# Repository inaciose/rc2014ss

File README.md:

# rc2014ss - RC2014 PCB single sided for CNC 3018
This repository was to be dedicated to sharing a series of board schematics and layouts compatible with the RC2014 bus and which were designed to be produced on a 3018 CNC.

However, I have had difficulty completing this project, but I have continued to make addon boards on perforated boards. Therefore, this repository became a generic place where I document the different boards.

Boards designed for CNC 3018

- Z80 CPU - rcz80cpu
- 32K RAM - rc32kram62256
- 64K RAM - rc64kram2x62256
- ACIA 6551 - rc6551z80
- ROM 2K - rcrom28c16
- ROM 8K - rcrom28c64
- ACIA 60b50 - rcserial60b50ttl
- Z80 tester - rcz80test

To make a minimal system with just boards made with the CNC 3018, the only thing left to do is a simple plate for the clock. In any case, I plan to make versions for the CNC 3018 of the main perforated plates in the long term.

# Board production process at CNC 3018

- Draw schematic in EAGLE
- Design the board within the size restrictions
- Export gerber files
- Import the copper_bottom.gbr file into flatcam and produce gcode files for track isolation
- Import the drill_1_16.xln file into flatcam and produce the gcode files to drill the holes
- Open the candle, and proceed with the alignment from scratch, load the isolation file, place the probe and make the height map, remove the probe, and start cnc it. When it stop, change the tool, load the hole drill file and move on.

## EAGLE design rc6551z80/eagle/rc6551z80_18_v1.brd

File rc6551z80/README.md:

# CNC 3018 - RC2014 - ACIA 6551 BOARD

This board is not covered in the stock SCM (Small computer monitor).

I have done a modified version of SCM that works with it. 
I also have modified a 2K z80 monitor to work with it.

TODO: need to collect the software...

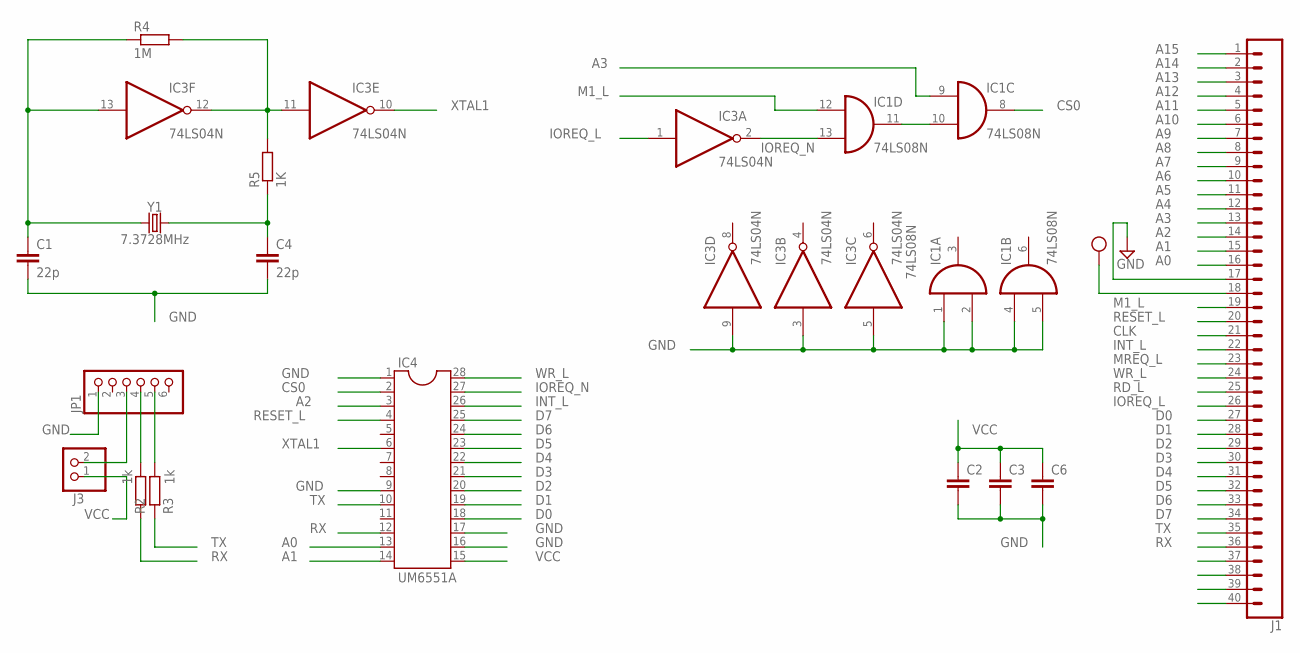
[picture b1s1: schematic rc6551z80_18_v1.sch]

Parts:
C1, C4: 22p; C025-024X044
C2, C3, C6: C-EU050-025X075; C050-025X075
IC1: 74LS08N; DIL14
IC3: 74LS04N; DIL14
IC4: UM6551A; DIL28-6
J1: CONN_40OFFSET; 1X40_OFFSET
J3: PINHD-1X2; 1X02
JP1: PINHD-1X6; 1X06
R2, R3: 1k; 0204/7
R4: 1M; 0204/7
R5: 1K; 0204/7
Y1: 7.3728MHz; HC49U

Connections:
A0: IC4.13, J1.16
A1: IC4.14, J1.15
A2: IC4.3, J1.14
A3: IC1.9 (I0), J1.13
A4: J1.12
A5: J1.11
A6: J1.10
A7: J1.9
A8: J1.8
A9: J1.7
A10: J1.6
A11: J1.5
A12: J1.4
A13: J1.3
A14: J1.2
A15: J1.1
CLK: J1.21
CS0: IC1.8 (O), IC4.2
D0: IC4.18, J1.27
D1: IC4.19, J1.28
D2: IC4.20, J1.29
D3: IC4.21, J1.30
D4: IC4.22, J1.31
D5: IC4.23, J1.32
D6: IC4.24, J1.33
D7: IC4.25, J1.34
GND: C1.2, C2.2, C3.2, C4.2, C6.2, IC1.1 (I0), IC1.2 (I1), IC1.4 (I0), IC1.5 (I1), IC1.7 (GND), IC3.3 (I), IC3.5 (I), IC3.7 (GND), IC3.9 (I), IC4.1, IC4.9, IC4.16, IC4.17, J1.17, JP1.1
INT_L: IC4.26, J1.22
IOREQ_L: IC3.1 (I), J1.26
IOREQ_N: IC1.13 (I1), IC3.2 (O), IC4.27
M1_L: IC1.12 (I0), J1.19
MREQ_L: J1.23
unnamed: J3.2, JP1.3
unnamed: JP1.4, R2.1
unnamed: JP1.5, R3.1
unnamed: C1.1, IC3.13 (I), R4.1, Y1.1
unnamed: C4.1, R5.1, Y1.2
unnamed: IC3.11 (I), IC3.12 (O), R4.2, R5.2
unnamed: IC1.10 (I1), IC1.11 (O)
RD_L: J1.25
RESET_L: IC4.4, J1.20
RX: IC4.12, J1.36, R2.2
TX: IC4.10, J1.35, R3.2
VCC: C2.1, C3.1, C6.1, IC1.14 (VCC), IC3.14 (VCC), IC4.15, J1.18, J3.1
WR_L: IC4.28, J1.24
XTAL1: IC3.10 (O), IC4.6

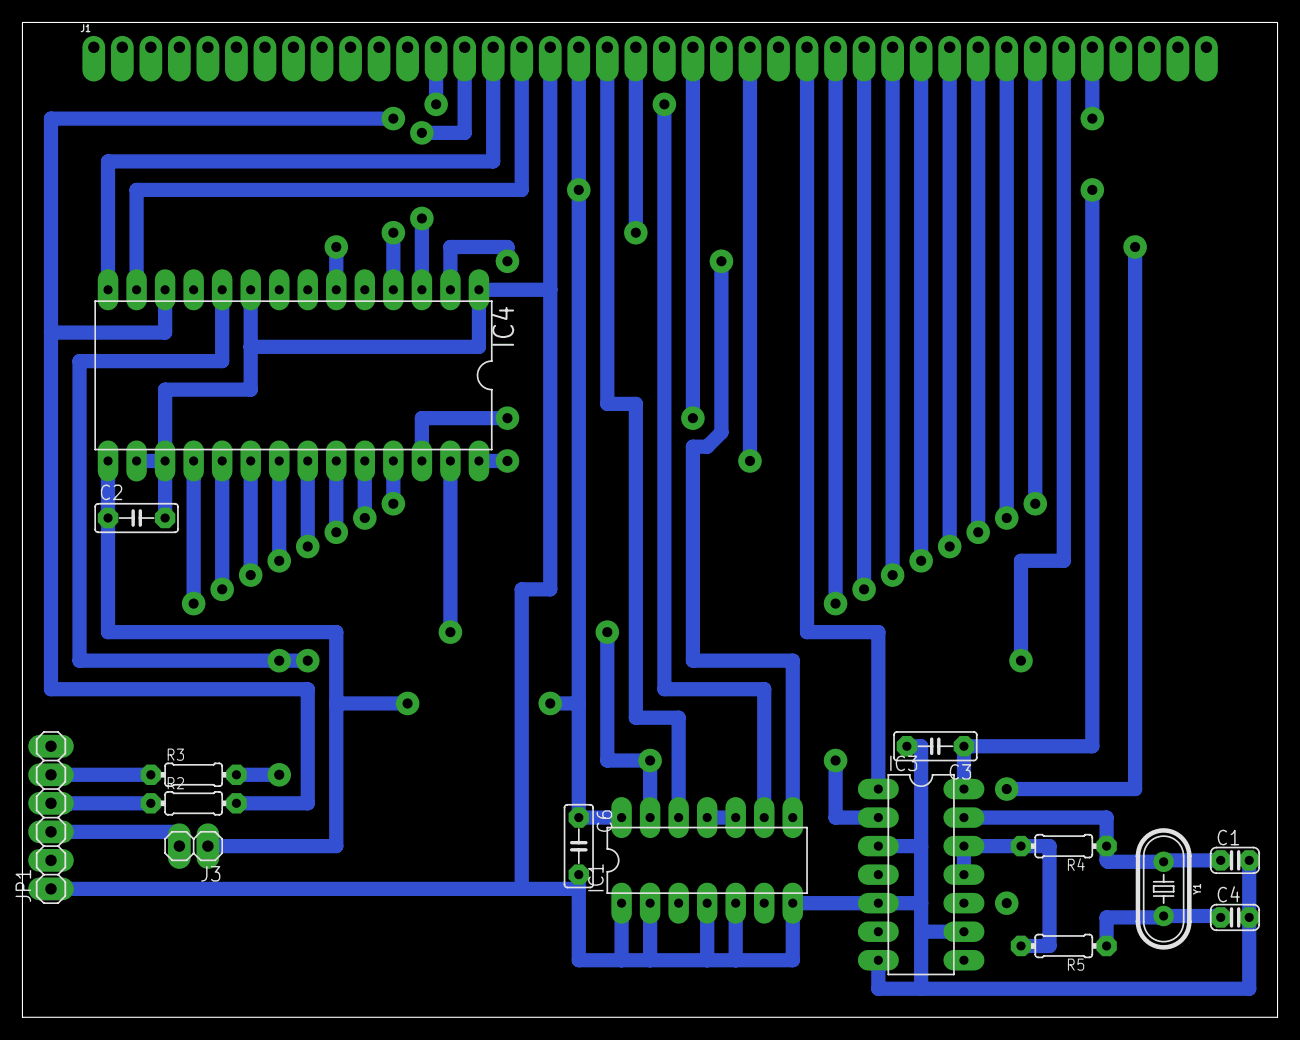
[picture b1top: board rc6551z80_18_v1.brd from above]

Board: 2 copper layers, 111.7 x 88.6 mm, 16 parts (0 on the bottom side), 31 nets.

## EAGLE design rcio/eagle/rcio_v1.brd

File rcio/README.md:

# CNC 3018 - RC2014 DIGITAL INPUT / OUTPUT BOARD

This board is done with one change face the schematics of the official RC2014 INPUT / OUTPUT BOARD

ICs
- 1 x 74LS273
- 1 x 74LS245
- 1 x 74LS138

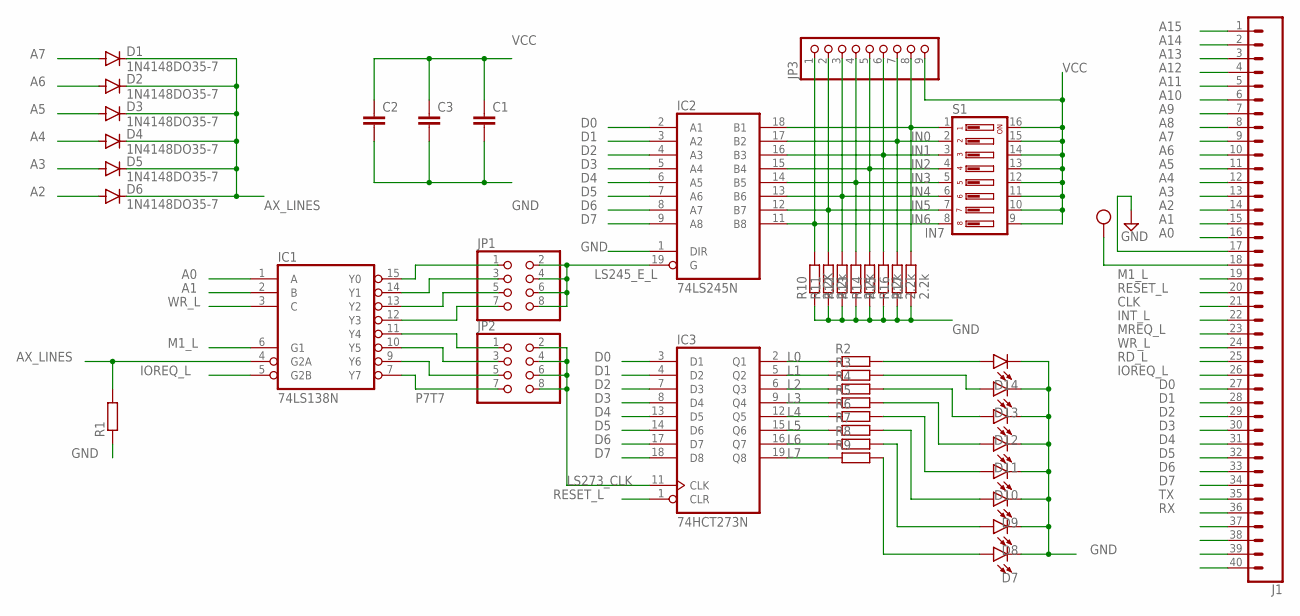
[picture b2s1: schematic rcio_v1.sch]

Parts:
C1, C2, C3: C-EU050-025X075; C050-025X075
D1, D2, D3, D4, D5, D6: 1N4148DO35-7; DO35-7
D7, D8, D9, D10, D11, D12, D13, D14: LED3MM; LED_3MM
IC1: 74LS138N; DIL16
IC2: 74LS245N; DIL20
IC3: 74HCT273N; DIL20
J1: CONN_40OFFSET; 1X40_OFFSET
JP1, JP2: PINHD-2X4; 2X04
JP3: PINHD-1X9; 1X09
R1, R2, R3, R4, R5, R6, R7, R8, R9, R12, R14: R-EU_0204/7; 0204/7
R10: 2.2K; 0204/7
R11, R13, R15, R16, R17: 2.2k; 0204/7
S1: DP08; DP-08

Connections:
A0: IC1.1 (A), J1.16
A1: IC1.2 (B), J1.15
A2: D6.A, J1.14
A3: D5.A, J1.13
A4: D4.A, J1.12
A5: D3.A, J1.11
A6: D2.A, J1.10
A7: D1.A, J1.9
A8: J1.8
A9: J1.7
A10: J1.6
A11: J1.5
A12: J1.4
A13: J1.3
A14: J1.2
A15: J1.1
AX_LINES: D1.C, D2.C, D3.C, D4.C, D5.C, D6.C, IC1.4 (G2A), R1.2
CLK: J1.21
D0: IC2.2 (A1), IC3.3 (D1), J1.27
D1: IC2.3 (A2), IC3.4 (D2), J1.28
D2: IC2.4 (A3), IC3.7 (D3), J1.29
D3: IC2.5 (A4), IC3.8 (D4), J1.30
D4: IC2.6 (A5), IC3.13 (D5), J1.31
D5: IC2.7 (A6), IC3.14 (D6), J1.32
D6: IC2.8 (A7), IC3.17 (D7), J1.33
D7: IC2.9 (A8), IC3.18 (D8), J1.34
GND: C1.2, C2.2, C3.2, D7.K (C), D8.K (C), D9.K (C), D10.K (C), D11.K (C), D12.K (C), D13.K (C), D14.K (C), IC1.8 (GND), IC2.1 (DIR), IC2.10 (GND), IC3.10 (GND), J1.17, R1.1, R10.1, R11.1, R12.1, R13.1, R14.1, R15.1, R16.1, R17.1
IN0: IC2.18 (B1), JP3.8, R17.2, S1.1
IN1: IC2.17 (B2), JP3.7, R16.2, S1.2
IN2: IC2.16 (B3), JP3.6, R15.2, S1.3
IN3: IC2.15 (B4), JP3.5, R14.2, S1.4
IN4: IC2.14 (B5), JP3.4, R13.2, S1.5
IN5: IC2.13 (B6), JP3.3, R12.2, S1.6
IN6: IC2.12 (B7), JP3.2, R11.2, S1.7
IN7: IC2.11 (B8), JP3.1, R10.2, S1.8
INT_L: J1.22
IOREQ_L: IC1.5 (G2B), J1.26
L0: IC3.2 (Q1), R2.1
L1: IC3.5 (Q2), R3.1
L2: IC3.6 (Q3), R4.1
L3: IC3.9 (Q4), R5.1
L4: IC3.12 (Q5), R6.1
L5: IC3.15 (Q6), R7.1
L6: IC3.16 (Q7), R8.1
L7: IC3.19 (Q8), R9.1
LED7: D7.A, R9.2
LS245_E_L: IC2.19 (G), JP1.2, JP1.4, JP1.6, JP1.8
LS273_CLK: IC3.11 (CLK), JP2.2, JP2.4, JP2.6, JP2.8
M1_L: IC1.6 (G1), J1.19
MREQ_L: J1.23
unnamed: IC1.15 (Y0), JP1.1
unnamed: IC1.14 (Y1), JP1.3
unnamed: IC1.13 (Y2), JP1.5
unnamed: IC1.12 (Y3), JP1.7
unnamed: IC1.11 (Y4), JP2.1
unnamed: IC1.10 (Y5), JP2.3
unnamed: IC1.9 (Y6), JP2.5
unnamed: D14.A, R2.2
unnamed: D13.A, R3.2
unnamed: D12.A, R4.2
unnamed: D11.A, R5.2
unnamed: D10.A, R6.2
unnamed: D9.A, R7.2
unnamed: D8.A, R8.2
P7T7: IC1.7 (Y7), JP2.7
RD_L: J1.25
RESET_L: IC3.1 (CLR), J1.20
RX: J1.36
TX: J1.35
VCC: C1.1, C2.1, C3.1, IC1.16 (VCC), IC2.20 (VCC), IC3.20 (VCC), J1.18, JP3.9, S1.9, S1.10, S1.11, S1.12, S1.13, S1.14, S1.15, S1.16
WR_L: IC1.3 (C), J1.24

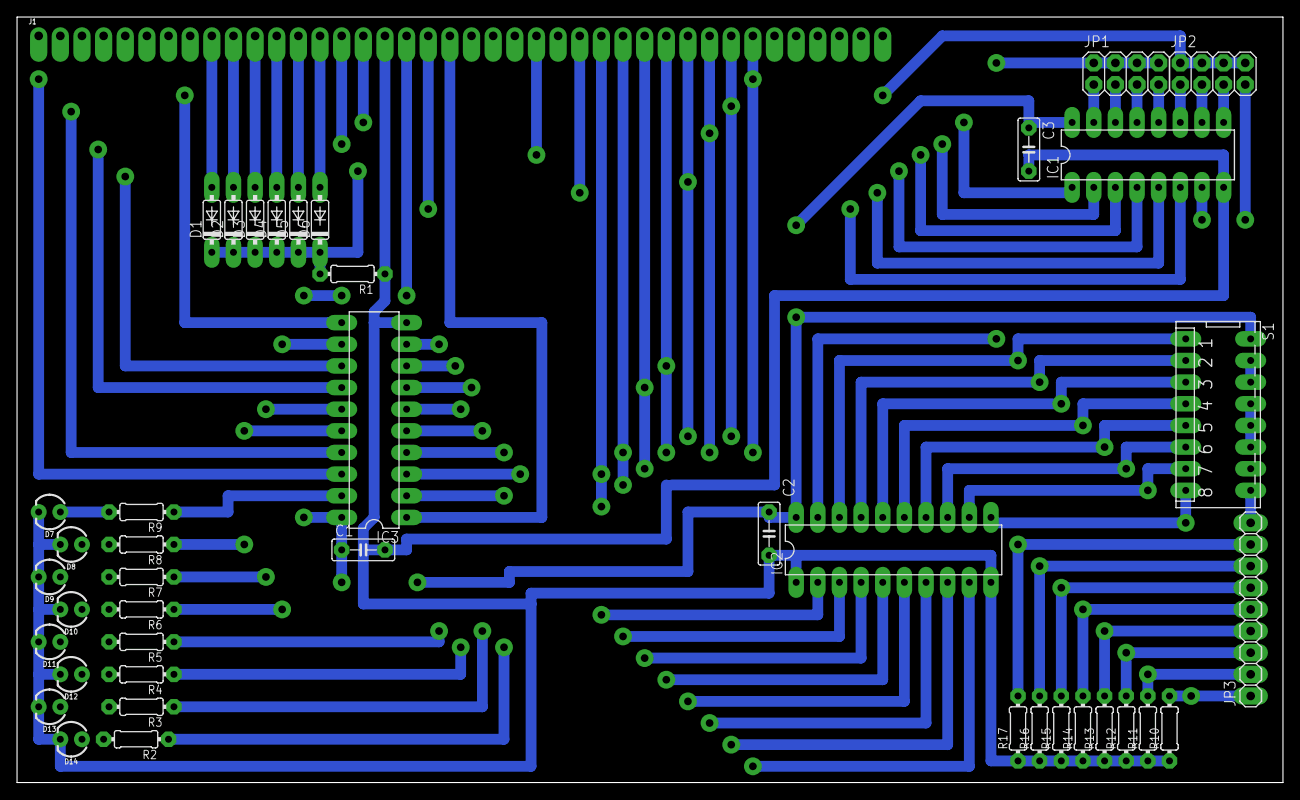
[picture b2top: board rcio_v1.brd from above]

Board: 2 copper layers, 148.6 x 89.8 mm, 42 parts (0 on the bottom side), 57 nets.

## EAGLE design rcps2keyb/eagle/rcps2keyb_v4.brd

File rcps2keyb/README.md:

# CNC 3018 - RC2014 - PS2 KEYBOARD BOARD

This board is done following the schematics of the cpuville.com ps2 keyboard interface

http://cpuville.com/Projects/Standalone-Z80-computer/images/keyboard-interface-schematic.jpg

This board needs some driver to be used. It is not integrated in any monitor.

TODO: get the z80 asm that can read the keyboard and display the chars on screen.

Not used in any computer

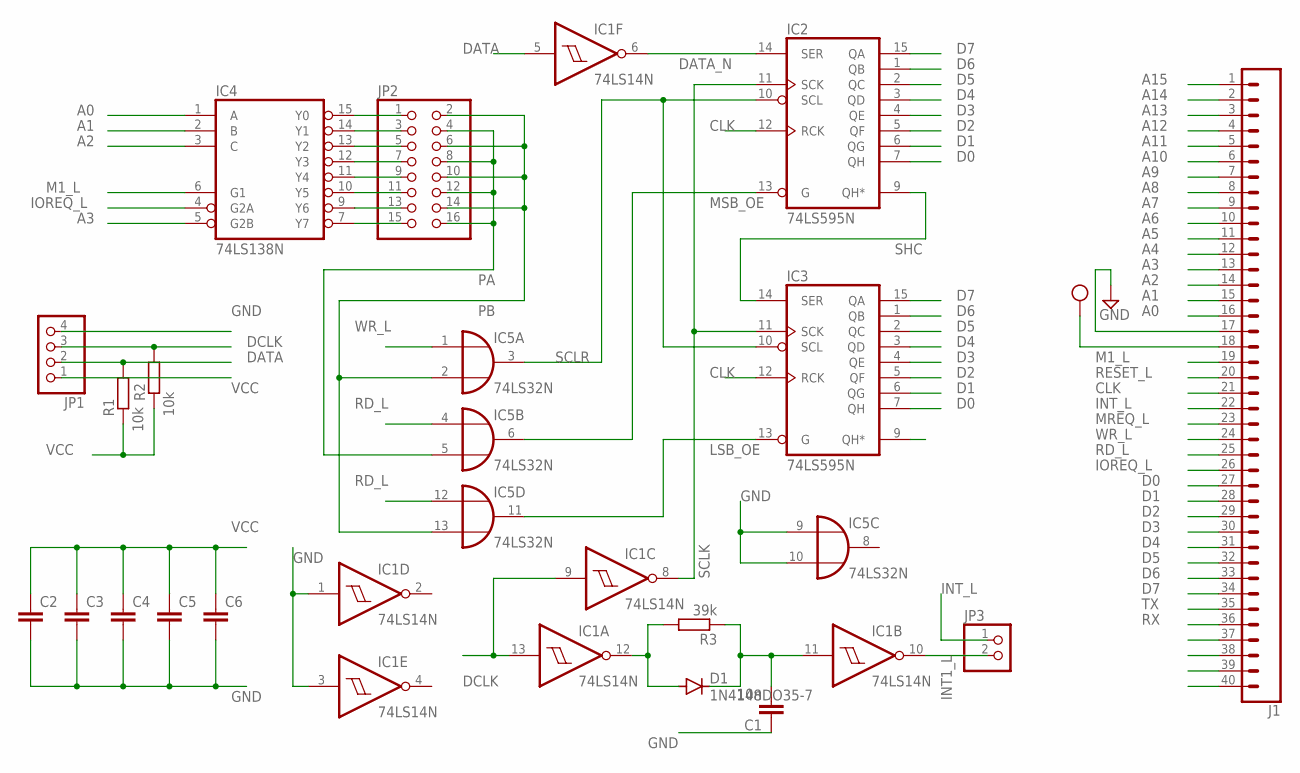
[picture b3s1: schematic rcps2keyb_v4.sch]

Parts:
C1: 10n; C050-025X075
C2, C3, C4, C5, C6: C-EU050-025X075; C050-025X075
D1: 1N4148DO35-7; DO35-7
IC1: 74LS14N; DIL14
IC2, IC3: 74LS595N; DIL16
IC4: 74LS138N; DIL16
IC5: 74LS32N; DIL14
J1: CONN_40OFFSET; 1X40_OFFSET
JP1: PINHD-1X4; 1X04
JP2: PINHD-2X8; 2X08
JP3: PINHD-1X2; 1X02
R1, R2: 10k; 0204/7
R3: 39k; 0204/7

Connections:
A0: IC4.1 (A), J1.16
A1: IC4.2 (B), J1.15
A2: IC4.3 (C), J1.14
A3: IC4.5 (G2B), J1.13
A4: J1.12
A5: J1.11
A6: J1.10
A7: J1.9
A8: J1.8
A9: J1.7
A10: J1.6
A11: J1.5
A12: J1.4
A13: J1.3
A14: J1.2
A15: J1.1
CLK: IC2.12 (RCK), IC3.12 (RCK), J1.21
D0: IC2.7 (QH), IC3.7 (QH), J1.27
D1: IC2.6 (QG), IC3.6 (QG), J1.28
D2: IC2.5 (QF), IC3.5 (QF), J1.29
D3: IC2.4 (QE), IC3.4 (QE), J1.30
D4: IC2.3 (QD), IC3.3 (QD), J1.31
D5: IC2.2 (QC), IC3.2 (QC), J1.32
D6: IC2.1 (QB), IC3.1 (QB), J1.33
D7: IC2.15 (QA), IC3.15 (QA), J1.34
DATA: IC1.5 (I), JP1.2, R1.2
DATA_N: IC1.6 (O), IC2.14 (SER)
DCLK: IC1.9 (I), IC1.13 (I), JP1.3, R2.2
GND: C1.1, C2.2, C3.2, C4.2, C5.2, C6.2, IC1.1 (I), IC1.3 (I), IC1.7 (GND), IC2.8 (GND), IC3.8 (GND), IC4.8 (GND), IC5.7 (GND), IC5.9 (I0), IC5.10 (I1), J1.17, JP1.4
INT1_L: IC1.10 (O), JP3.2
INT_L: J1.22, JP3.1
IOREQ_L: IC4.4 (G2A), J1.26
LSB_OE: IC3.13 (G), IC5.11 (O)
M1_L: IC4.6 (G1), J1.19
MREQ_L: J1.23
MSB_OE: IC2.13 (G), IC5.6 (O)
unnamed: D1.A, IC1.12 (O), R3.2
unnamed: C1.2, D1.C, IC1.11 (I), R3.1
unnamed: IC4.7 (Y7), JP2.15
unnamed: IC4.9 (Y6), JP2.13
unnamed: IC4.10 (Y5), JP2.11
unnamed: IC4.15 (Y0), JP2.1
unnamed: IC4.14 (Y1), JP2.3
unnamed: IC4.13 (Y2), JP2.5
unnamed: IC4.12 (Y3), JP2.7
unnamed: IC4.11 (Y4), JP2.9
PA: IC5.5 (I1), JP2.4, JP2.8, JP2.12, JP2.16
PB: IC5.2 (I1), IC5.13 (I1), JP2.2, JP2.6, JP2.10, JP2.14
RD_L: IC5.4 (I0), IC5.12 (I0), J1.25
RESET_L: J1.20
RX: J1.36
SCLK: IC1.8 (O), IC2.11 (SCK), IC3.11 (SCK)
SCLR: IC2.10 (SCL), IC3.10 (SCL), IC5.3 (O)
SHC: IC2.9 (QH*), IC3.14 (SER)
TX: J1.35
VCC: C2.1, C3.1, C4.1, C5.1, C6.1, IC1.14 (VCC), IC2.16 (VCC), IC3.16 (VCC), IC4.16 (VCC), IC5.14 (VCC), J1.18, JP1.1, R1.1, R2.1
WR_L: IC5.1 (I0), J1.24

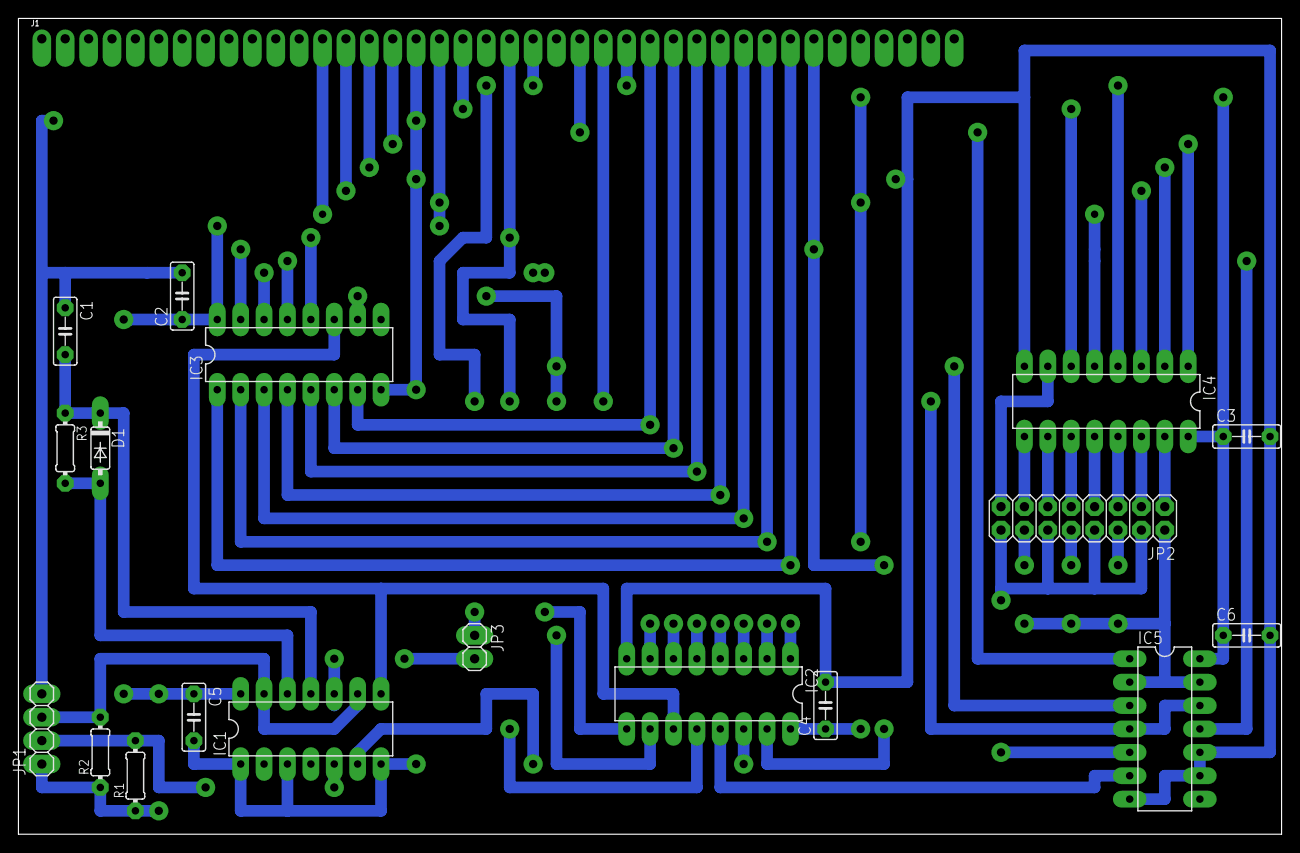
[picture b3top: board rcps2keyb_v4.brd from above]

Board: 2 copper layers, 137.1 x 88.6 mm, 19 parts (0 on the bottom side), 41 nets.

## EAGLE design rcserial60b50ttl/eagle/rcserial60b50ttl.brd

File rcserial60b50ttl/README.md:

# CNC 3013 - RC2014 - ACIA MC68b50 BOARD

# There is also a perfboard version

Placa de comunicação serie com o MC68B50 e relógio interno (1.8G) 56000N1
Feita em perfboard.
Pode ser configurada (jumper) para funcionar com o relógio externo ou interno)

Com a placa com os pinos para baixo

ELI
0== Relogio interno
==0 relógio externo

Os pinos existentes não cobrem o barramento todo. Encaixar com cuidado.

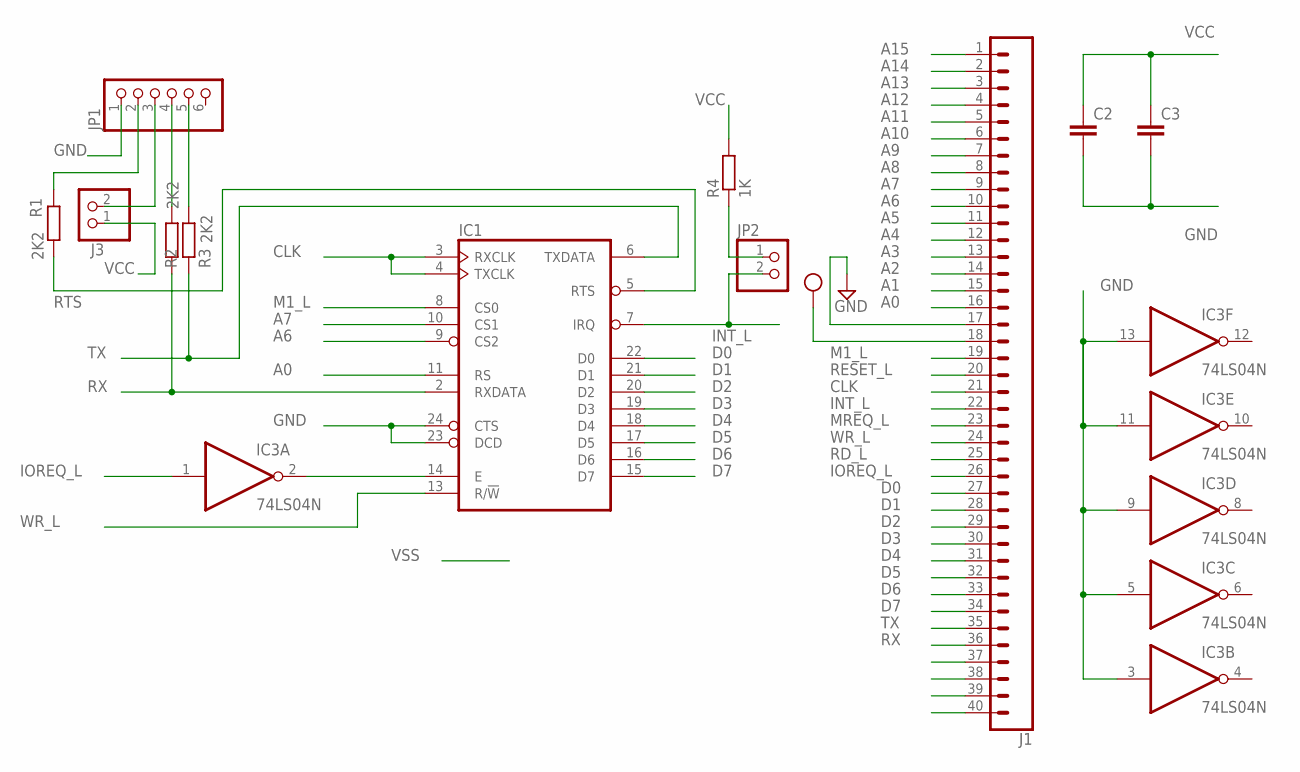
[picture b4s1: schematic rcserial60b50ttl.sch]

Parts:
C2, C3: C-EU050-025X075; C050-025X075
IC1: 6850; DIL24
IC3: 74LS04N; DIL14
J1: CONN_40OFFSET; 1X40_OFFSET
J3: PINHD-1X2; 1X02
JP1: PINHD-1X6; 1X06
JP2: PINHD-1X2; 1X02
R1, R2, R3: 2K2; 0204/7
R4: 1K; 0204/7

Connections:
A0: IC1.11 (RS), J1.16
A1: J1.15
A2: J1.14
A3: J1.13
A4: J1.12
A5: J1.11
A6: IC1.9 (CS2), J1.10
A7: IC1.10 (CS1), J1.9
A8: J1.8
A9: J1.7
A10: J1.6
A11: J1.5
A12: J1.4
A13: J1.3
A14: J1.2
A15: J1.1
CLK: IC1.3 (RXCLK), IC1.4 (TXCLK), J1.21
D0: IC1.22 (D0), J1.27
D1: IC1.21 (D1), J1.28
D2: IC1.20 (D2), J1.29
D3: IC1.19 (D3), J1.30
D4: IC1.18 (D4), J1.31
D5: IC1.17 (D5), J1.32
D6: IC1.16 (D6), J1.33
D7: IC1.15 (D7), J1.34
GND: C2.2, C3.2, IC1.23 (DCD), IC1.24 (CTS), IC3.3 (I), IC3.5 (I), IC3.7 (GND), IC3.9 (I), IC3.11 (I), IC3.13 (I), J1.17, JP1.1
INT_L: IC1.7 (IRQ), J1.22, JP2.2
IOREQ_L: IC3.1 (I), J1.26
M1_L: IC1.8 (CS0), J1.19
MREQ_L: J1.23
unnamed: IC1.14 (E), IC3.2 (O)
unnamed: JP1.2, R1.1
unnamed: J3.2, JP1.3
unnamed: JP1.4, R2.1
unnamed: JP1.5, R3.1
unnamed: JP2.1, R4.1
RD_L: J1.25
RESET_L: J1.20
RTS: IC1.5 (RTS), R1.2
RX: IC1.2 (RXDATA), J1.36, R2.2
TX: IC1.6 (TXDATA), J1.35, R3.2
VCC: C2.1, C3.1, IC1.12 (VCC), IC3.14 (VCC), J1.18, J3.1, R4.2
VSS: IC1.1 (VSS)
WR_L: IC1.13 (R/!W), J1.24

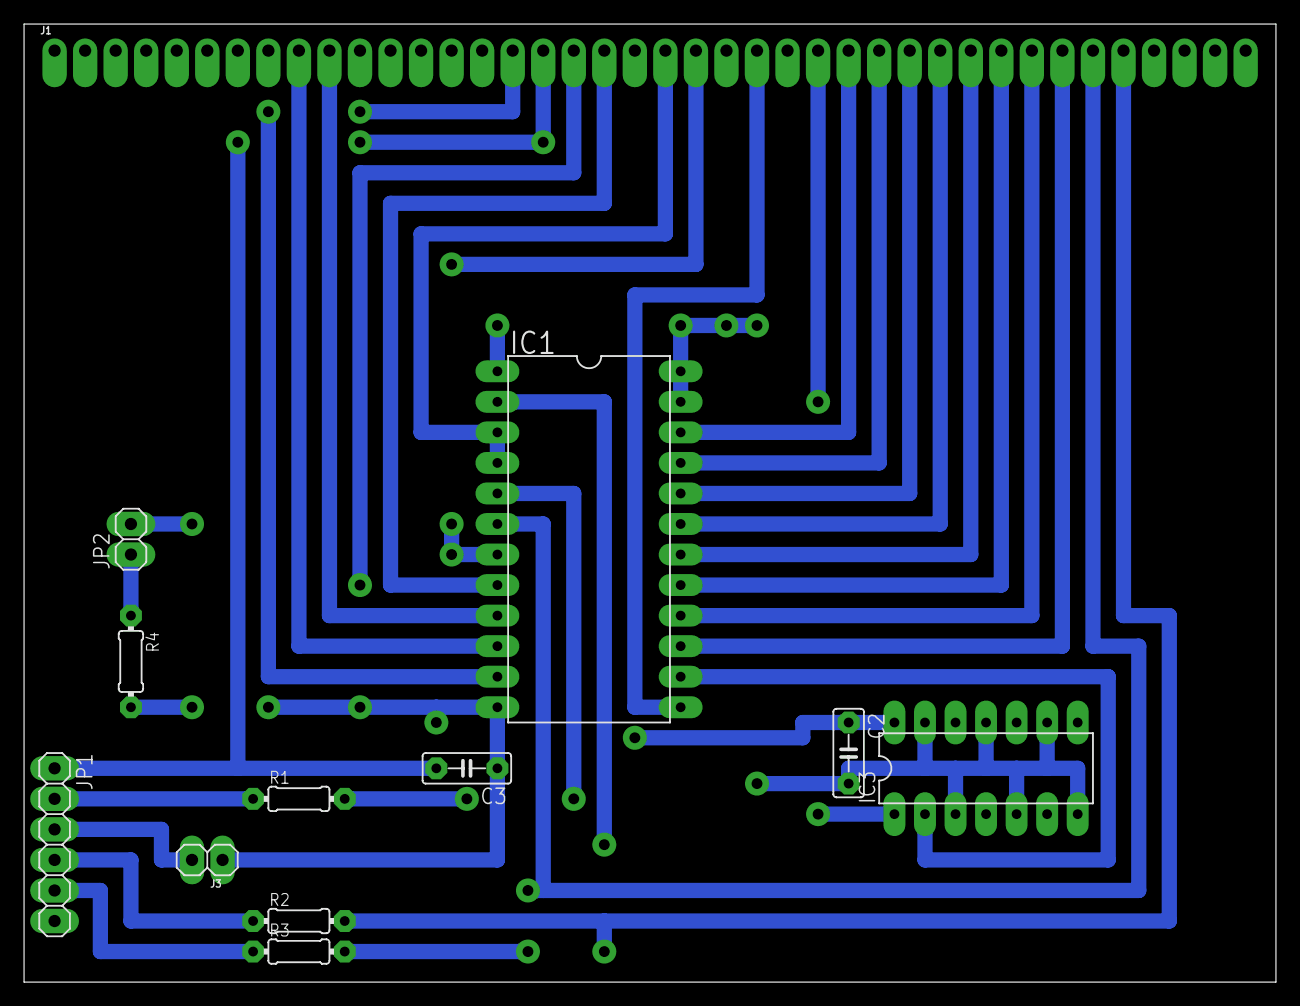
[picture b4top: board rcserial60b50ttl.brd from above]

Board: 2 copper layers, 104.1 x 79.7 mm, 12 parts (0 on the bottom side), 27 nets.

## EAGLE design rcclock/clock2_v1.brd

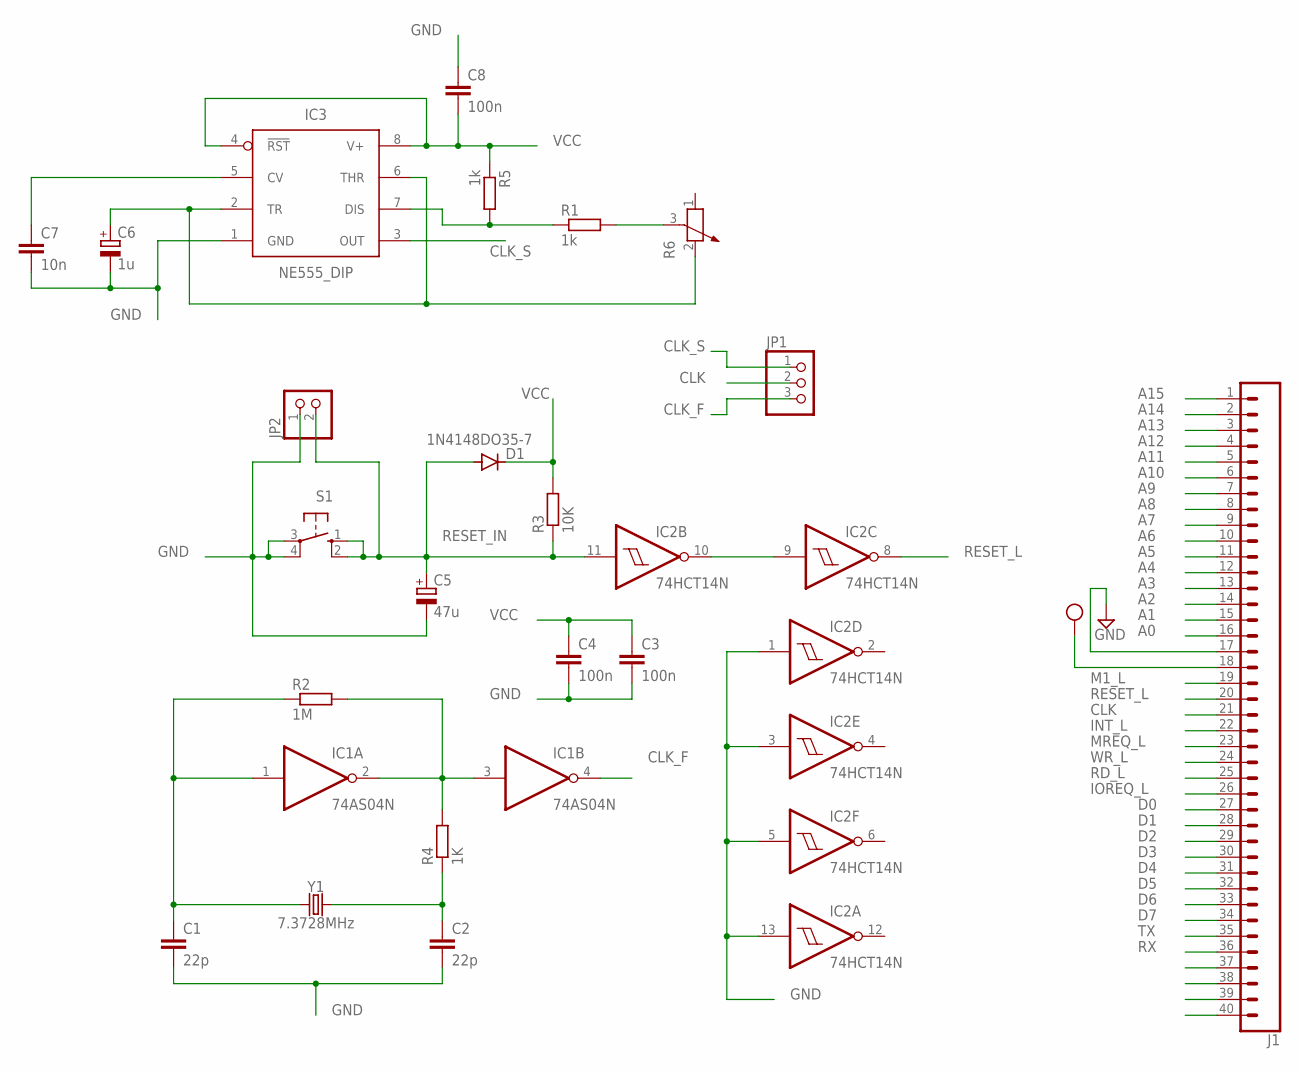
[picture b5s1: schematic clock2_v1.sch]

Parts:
C1, C2: 22p; C025-024X044
C3, C4: 100n; C025-024X044
C5: 47u; E2,5-5
C6: 1u; E2,5-5
C7: 10n; C050-025X075
C8: 100n; C050-025X075
D1: 1N4148DO35-7; DO35-7
IC1: 74AS04N; DIL14
IC2: 74HCT14N; DIL14
IC3: NE555_DIP; DIP826W53P254L959H508Q8B
J1: CONN_40OFFSET; 1X40_OFFSET
JP1: PINHD-1X3; 1X03
JP2: PINHD-1X2; 1X02
R1, R5: 1k; 0207/7
R2: 1M; 0204/5
R3: 10K; 0207/7
R4: 1K; 0204/5
R6: POTENTIOMETER_PT-10S; PT-10S
S1: 10-XX; B3F-10XX
Y1: 7.3728MHz; HC49U

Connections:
A0: J1.16
A1: J1.15
A2: J1.14
A3: J1.13
A4: J1.12
A5: J1.11
A6: J1.10
A7: J1.9
A8: J1.8
A9: J1.7
A10: J1.6
A11: J1.5
A12: J1.4
A13: J1.3
A14: J1.2
A15: J1.1
CLK: J1.21, JP1.2
CLK_F: IC1.4 (O), JP1.3
CLK_S: IC3.3 (OUT), JP1.1
D0: J1.27
D1: J1.28
D2: J1.29
D3: J1.30
D4: J1.31
D5: J1.32
D6: J1.33
D7: J1.34
GND: C1.2, C2.2, C3.2, C4.2, C5.-, C6.-, C7.2, C8.1, IC1.7 (GND), IC2.1 (I), IC2.3 (I), IC2.5 (I), IC2.7 (GND), IC2.13 (I), IC3.1 (GND), J1.17, JP2.1, S1.3, S1.4 (P1)
INT_L: J1.22
IOREQ_L: J1.26
M1_L: J1.19
MREQ_L: J1.23
unnamed: C1.1, IC1.1 (I), R2.1, Y1.1
unnamed: C2.1, R4.1, Y1.2
unnamed: C7.1, IC3.5 (CV)
unnamed: IC1.2 (O), IC1.3 (I), R2.2, R4.2
unnamed: IC2.9 (I), IC2.10 (O)
unnamed: C6.+, IC3.2 (TR), IC3.6 (THR), R6.2
unnamed: IC3.7 (DIS), R1.1, R5.2
unnamed: R1.2, R6.3
RD_L: J1.25
RESET_IN: C5.+, D1.A, IC2.11 (I), JP2.2, R3.1, S1.1 (S), S1.2 (S1)
RESET_L: IC2.8 (O), J1.20
RX: J1.36
TX: J1.35
VCC: C3.1, C4.1, C8.2, D1.C, IC1.14 (VCC), IC2.14 (VCC), IC3.4 (!RST), IC3.8 (V+), J1.18, R3.2, R5.1
WR_L: J1.24

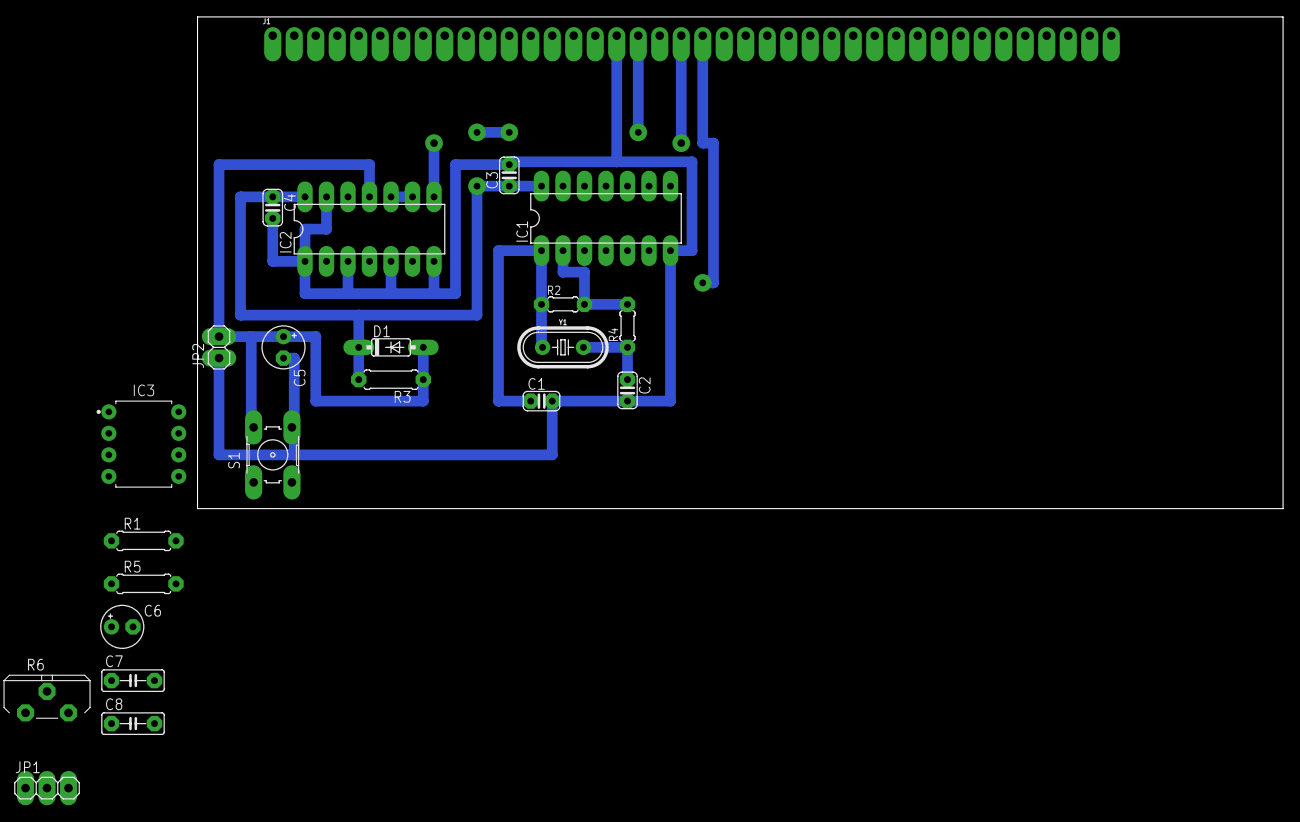
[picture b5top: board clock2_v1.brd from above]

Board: 2 copper layers, 128.2 x 58.1 mm, 23 parts (0 on the bottom side), 15 nets.

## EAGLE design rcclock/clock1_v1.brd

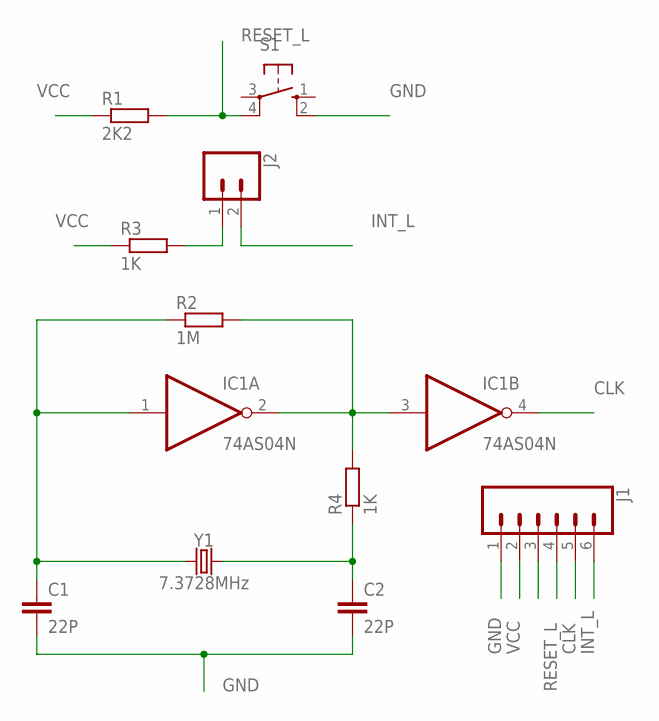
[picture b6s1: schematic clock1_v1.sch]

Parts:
C1, C2: 22P; C025-024X044
IC1: 74AS04N; DIL14
J1: CONN_06LONGPADS; 1X06_LONGPADS
J2: CONN_02PTH3; 1X02_LONGPADS
R1: 2K2; 0204/5
R2: 1M; 0204/5
R3, R4: 1K; 0204/5
S1: 10-XX; B3F-10XX
Y1: 7.3728MHz; HC49U

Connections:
CLK: IC1.4 (O), J1.5
GND: C1.2, C2.2, IC1.7 (GND), J1.1, S1.2 (S1)
INT_L: J1.6, J2.2
unnamed: C1.1, IC1.1 (I), R2.1, Y1.1
unnamed: C2.1, R4.1, Y1.2
unnamed: IC1.2 (O), IC1.3 (I), R2.2, R4.2
unnamed: J2.1, R3.2
RESET_L: J1.4, R1.2, S1.4 (P1)
VCC: IC1.14 (VCC), J1.2, R1.1, R3.1

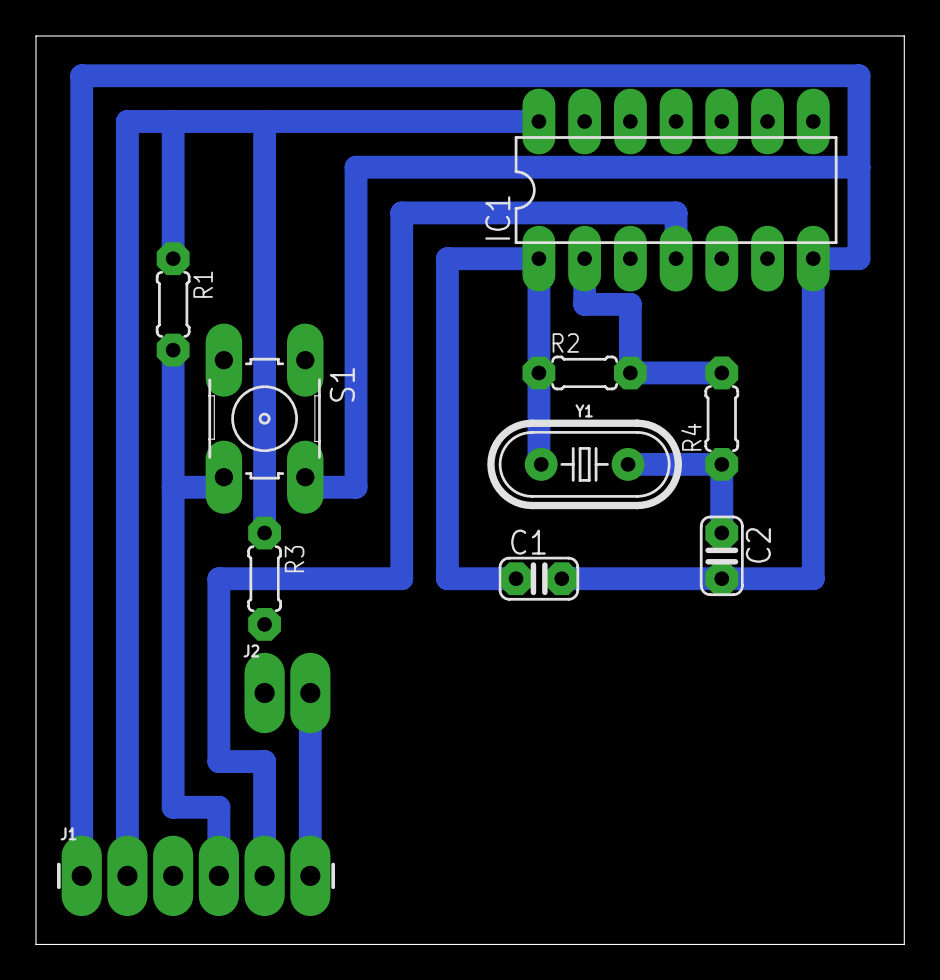
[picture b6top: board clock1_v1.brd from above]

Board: 2 copper layers, 48.2 x 50.5 mm, 11 parts (0 on the bottom side), 9 nets.

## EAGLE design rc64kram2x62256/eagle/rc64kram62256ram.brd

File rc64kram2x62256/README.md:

# CNC 3018 - RC2014 - 64K RAM BOARD

This board is done following the schematics of the official RC2014-32K RAM (now retired)

ICs
- 2 x 62256 RAM
- 2 x 74LS32
- 1 x 74LS04

Sockets
- 2 x 28 pin wide DIL
- 3 x 14 pin narrow DIL

Jumpers de configuração
JP - Entrada PAGE (quando não está disponivel, ligar VCC)
G = gnd
P = Page
V = VCC (5V)
I = imput sinal page

Pela ordem da placa (com os pinos para baixo)
         GPV
Sem page 0==
com page 0I0

J1+J2+J3 - Configuração do endereço inicial

SA   ROMS RAMS        qL3   qL4   qLg
1000 4K   28K - 60K   ==0   ==0   ==0
2000 8K   24K - 56K   0==   ==0   ==0
4000 16K  16K - 48K   XXX   0==   ==0
0000      32K - 64K   XXX   XXX   0==

Pela ordem da placa (com os pinos para baixo)

Creio que esta está bem
Config com: J4 Normal (page ignorado) 0==

SA 0000 1000 2000 4000 (RAM address start)
J1 ==0  0==  XXX  XXX
J2 ==0  ==0  0==  XXX
J3 ==0  ==0  ==0  0==
RS 0    4K   8K   16K (ROM size, start at 0000)
MS 32K  28K  24K  16K (Low RAM size available)
MH 32K  32K  32K  32K (High RAM size available)
MT 64K  60K  56K  48K (Total RAM available, 64K need page active)

Para 64K RAM activa, a ROM tem de estar inactiva, ou seja:
SA 0000, obriga a que o J4 ==0 (Com page) 
Quer-me parece que com o suporte para page activado,
a unica configuração que faz sentido é a SA 0000
Pois quando a:
- ROM está ativa, PAGE LOW, O CS_L fica HIGH, mesmo que o resultado da selecção dos J1, J2, J3, seja LOW. Low RAM inactiva.
- ROM está inativa, PAGE HIGH, O CS_L fica HIGH, só se o resultado da selecção dos J1, J2, J3, seja HIGH. Low RAM activa dependente do endereço.

Ou seja, com a ROM inactiva, se o SA > 0000, o espaço de endereçamento entre 0000 e o SA selecionado, fica não atribuido, pelo que só faz sentido SA = 0000. 

J4 - seleção do modo page ou normal
O modo page, para funcionar adequadamente implica a existencia da entrada do sinal no J0

Pela ordem da placa (com os pinos para baixo)
                    PLN
Normal (sem page) 0== 
Com page          ==0

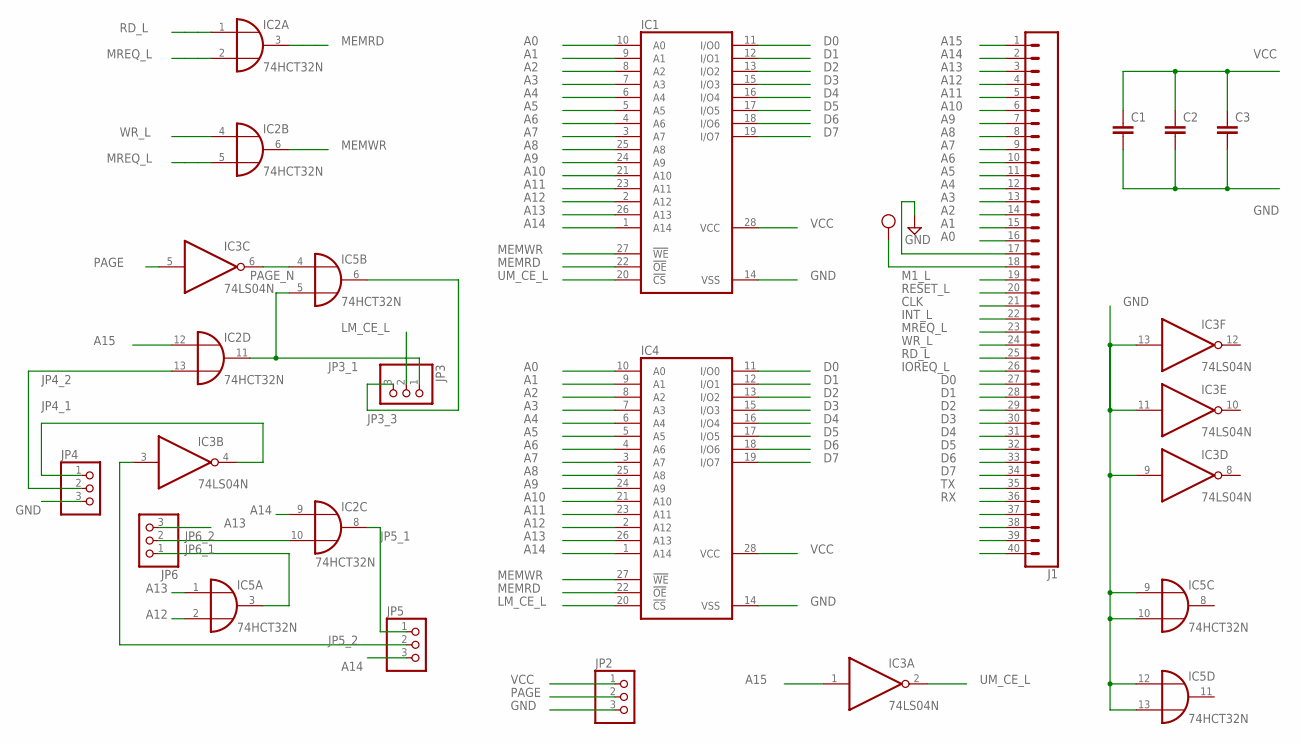
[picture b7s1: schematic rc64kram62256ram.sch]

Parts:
C1, C2, C3: C-EU050-025X075; C050-025X075
IC1, IC4: 62256P; DIL28-6
IC2, IC5: 74HCT32N; DIL14
IC3: 74LS04N; DIL14
J1: CONN_40OFFSET; 1X40_OFFSET
JP2, JP3, JP4, JP5, JP6: PINHD-1X3; 1X03

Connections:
A0: IC1.10 (A0), IC4.10 (A0), J1.16
A1: IC1.9 (A1), IC4.9 (A1), J1.15
A2: IC1.8 (A2), IC4.8 (A2), J1.14
A3: IC1.7 (A3), IC4.7 (A3), J1.13
A4: IC1.6 (A4), IC4.6 (A4), J1.12
A5: IC1.5 (A5), IC4.5 (A5), J1.11
A6: IC1.4 (A6), IC4.4 (A6), J1.10
A7: IC1.3 (A7), IC4.3 (A7), J1.9
A8: IC1.25 (A8), IC4.25 (A8), J1.8
A9: IC1.24 (A9), IC4.24 (A9), J1.7
A10: IC1.21 (A10), IC4.21 (A10), J1.6
A11: IC1.23 (A11), IC4.23 (A11), J1.5
A12: IC1.2 (A12), IC4.2 (A12), IC5.2 (I1), J1.4
A13: IC1.26 (A13), IC4.26 (A13), IC5.1 (I0), J1.3, JP6.3
A14: IC1.1 (A14), IC2.9 (I0), IC4.1 (A14), J1.2, JP5.3
A15: IC2.12 (I0), IC3.1 (I), J1.1
CLK: J1.21
D0: IC1.11 (I/O0), IC4.11 (I/O0), J1.27
D1: IC1.12 (I/O1), IC4.12 (I/O1), J1.28
D2: IC1.13 (I/O2), IC4.13 (I/O2), J1.29
D3: IC1.15 (I/O3), IC4.15 (I/O3), J1.30
D4: IC1.16 (I/O4), IC4.16 (I/O4), J1.31
D5: IC1.17 (I/O5), IC4.17 (I/O5), J1.32
D6: IC1.18 (I/O6), IC4.18 (I/O6), J1.33
D7: IC1.19 (I/O7), IC4.19 (I/O7), J1.34
GND: C1.2, C2.2, C3.2, IC1.14 (VSS), IC2.7 (GND), IC3.7 (GND), IC3.9 (I), IC3.11 (I), IC3.13 (I), IC4.14 (VSS), IC5.7 (GND), IC5.9 (I0), IC5.10 (I1), IC5.12 (I0), IC5.13 (I1), J1.17, JP2.3, JP4.3
INT_L: J1.22
IOREQ_L: J1.26
JP3_1: IC2.11 (O), IC5.5 (I1), JP3.1
JP3_3: IC5.6 (O), JP3.3
JP4_1: IC3.4 (O), JP4.1
JP4_2: IC2.13 (I1), JP4.2
JP5_1: IC2.8 (O), JP5.1
JP5_2: IC3.3 (I), JP5.2
JP6_1: IC5.3 (O), JP6.1
JP6_2: IC2.10 (I1), JP6.2
LM_CE_L: IC4.20 (!CS), JP3.2
M1_L: J1.19
MEMRD: IC1.22 (!OE), IC2.3 (O), IC4.22 (!OE)
MEMWR: IC1.27 (!WE), IC2.6 (O), IC4.27 (!WE)
MREQ_L: IC2.2 (I1), IC2.5 (I1), J1.23
PAGE: IC3.5 (I), JP2.2
PAGE_N: IC3.6 (O), IC5.4 (I0)
RD_L: IC2.1 (I0), J1.25
RESET_L: J1.20
RX: J1.36
TX: J1.35
UM_CE_L: IC1.20 (!CS), IC3.2 (O)
VCC: C1.1, C2.1, C3.1, IC1.28 (VCC), IC2.14 (VCC), IC3.14 (VCC), IC4.28 (VCC), IC5.14 (VCC), J1.18, JP2.1
WR_L: IC2.4 (I0), J1.24

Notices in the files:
parts and their libraries:
SparkFun-Connectors: Licensing: Creative Commons ShareAlike 4.0 International - https://creativecommons.org/licenses/by-sa/4.0
